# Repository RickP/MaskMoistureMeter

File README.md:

# MaskMoistureMeter

## About this project

A simple device that measures the moisture of face masks. It uses a 555 timer to measure the resistance of cloth.

If the mask is dry, it lights up a green LED. If the mask is moist it blinks a red LED and also beeps with a piezo buzzer.
The faster is blinks and the higher the beepers pitch the more moisture is in your mask.

Replace and/or wash moist masks immediately as wearing a wet mask is dangerous to your health.

The electronics was designed in KiCad and has all information tor order it assembled from JLCPCB.

## Project files

- case: The case as a step and stl file
- fabrication: Gerbers, bom and pick and place files, made according to the JLCPCB free SMT assembly specs
- images: Some images of the PCB, assembled PCB and the case
- pcb: KiCad project files

## PCB specs

- 2 layers FR4
- EIG finish recommended so the sensor area doesn't oxidize
- Board thickness 1mm - otherwise it won't fit the included case

## Parts

### BT1
Battery holder for a CR2032 coin cell. Alternative to LCSC part: Keystone 1060.

### BZ1
The buzzer. Murata PKMCS0909E4000-R1 - can be left out for LED indication only.

### C1 and C2
100nf 0603 capacitor. Use any one with at least 5% tolerance and 6.3V voltage rating.

### D1 and D2
0805 LED in green (D1) and red (D2). Use LEDs with a forward voltage of under 2.8V.

### R1 and R2
0603 resistor with about 150 ohm. Adjust to tune the brightness of your LEDs.

### R3
0603 resistor with 1k.

### SW1
5.1x5.1mm SMD push button with gullwing pins and a height of 3 to 3.5mm.
Alternatives to the LCSC part: Würth 430451035836 or C&K KSC341GLFS

### U1
555 timer IC in 8-SOIC package that works at 2V.
You can use: TLC555CDR, TLC555IDR, TLC555QDR or TLC555CD

## Video Demo

[See it in action here](https://www.youtube.com/watch?v=zS53NGnmHDQ)

## Assembled device in case

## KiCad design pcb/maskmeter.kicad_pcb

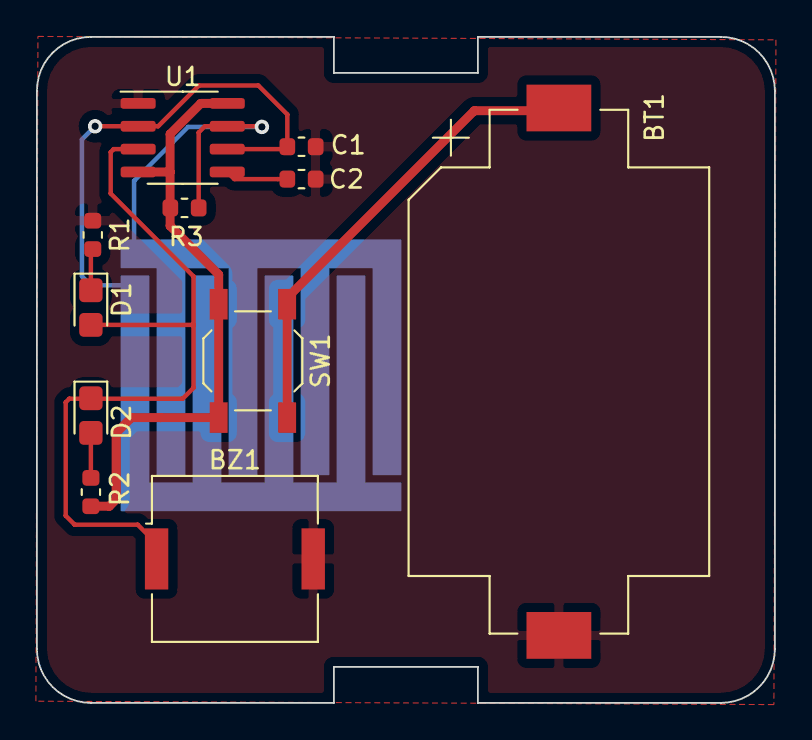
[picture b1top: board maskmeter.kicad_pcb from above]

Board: 2 copper layers, 41.0 x 37.0 mm, 12 parts (1 on the bottom side), 9 nets.

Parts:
BT1: Battery_Cell; BatteryHolder_Keystone_1060_1x2032
BZ1: Buzzer; Buzzer_Murata_PKMCS0909E4000-R1
C1, C2: 0.1uF; C_0603_1608Metric
D1: YELLOW; LED_0805_2012Metric_Castellated
D2: RED; LED_0805_2012Metric_Castellated
R1, R2: R75; R_0603_1608Metric
R3: 1k; R_0603_1608Metric
R4: R_PCB; PCB_Resistance_Pad
SW1: SW_Push; SW_SPST_TL3342
U1: TLC555IDR; SOIC-8_3.9x4.9mm_P1.27mm

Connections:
GND: BT1.2, BZ1.2, C1.1, C2.2, R1.2, U1.1
unnamed: BT1.1, SW1.1
unnamed: BZ1.1, D1.2, D2.1, U1.3
unnamed: C1.2, R4.1, U1.2, U1.6
unnamed: C2.1, U1.5
unnamed: D1.1, R1.1
unnamed: D2.2, R2.2
unnamed: R3.2, R4.2, U1.7
VCC: R2.1, R3.1, SW1.2, U1.4, U1.8

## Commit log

2020-05-18 init
2020-05-31 Updated battery holder
2020-05-31 Reorganized files
2020-05-31 Added fabrication files
2020-05-31 Added case
2020-05-31 Updates gerbers
2020-05-31 Changed resitors and green LED
2020-05-31 Added images
2020-06-01 Extended README
2020-06-09 Changed video link
2020-11-06 Set PCB thickness to 1mm
2020-12-22 Revert "Set PCB thickness to 1mm"
    This reverts commit 019fabce52c92cc1307a1fe131da5ab49f218db2.
2020-12-22 Redid last commit in Kicad 5 (instead of nightly)
